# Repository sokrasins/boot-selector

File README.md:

# Boot Selector
 
 Choose your booting OS, now with more RP2040!

 Inspired by

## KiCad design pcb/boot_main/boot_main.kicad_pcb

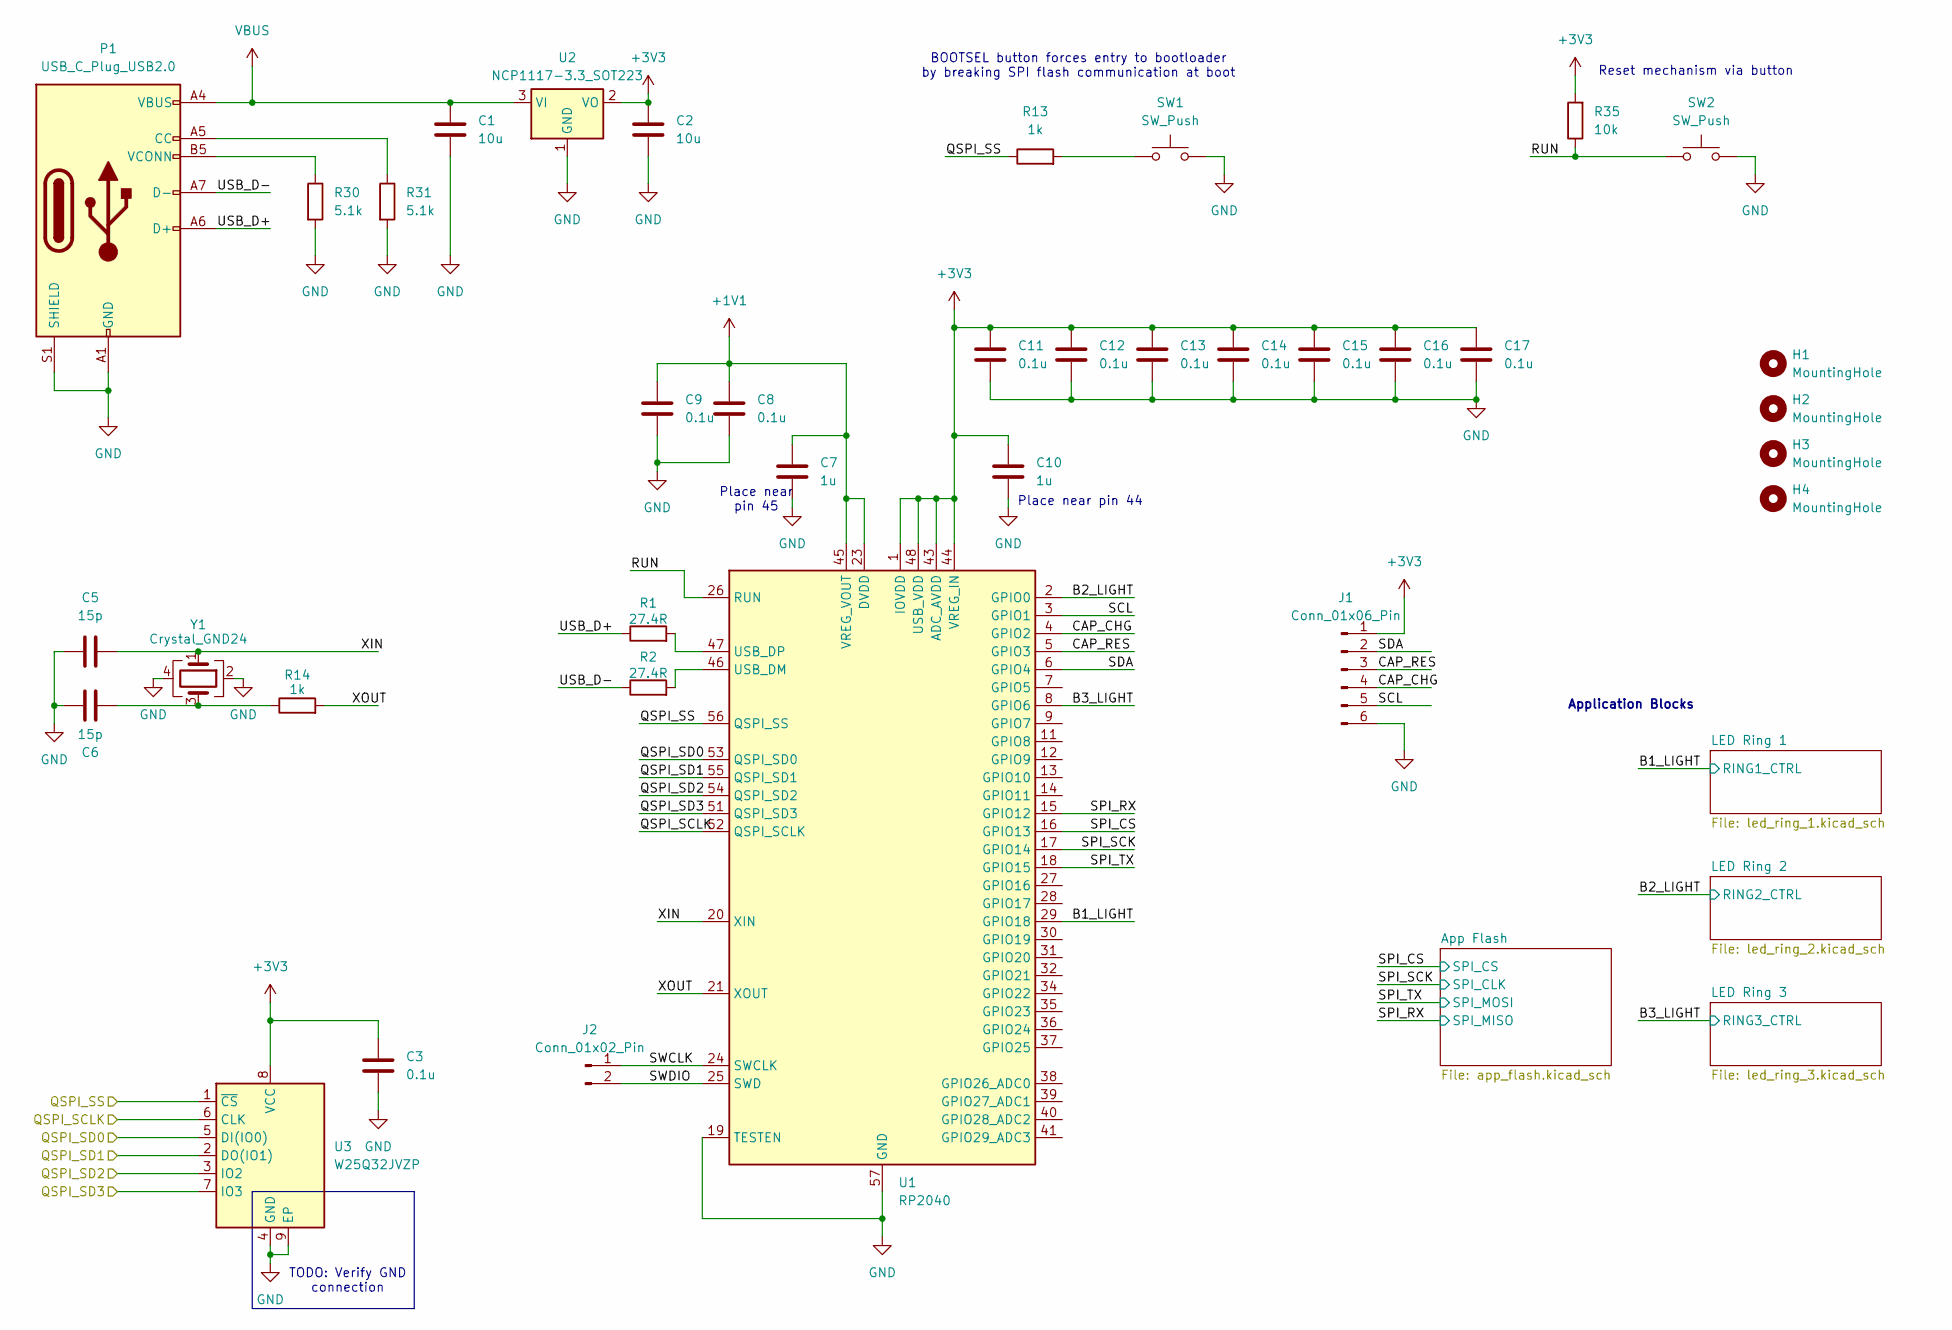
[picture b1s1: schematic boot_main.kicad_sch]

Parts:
C1, C2: 10u; C_0603_1608Metric
C3: 0.1u; C_0603_1608Metric
C5, C6: 15p; C_0402_1005Metric
C7, C10: 1u; C_0402_1005Metric
C8, C9, C11, C12, C13, C14, C15, C16, C17: 0.1u; C_0402_1005Metric
H1, H2, H3, H4: MountingHole; MountingHole_3.2mm_M3
J1: Conn_01x06_Pin; Hirose_FH12-6S-0.5SH_1x06-1MP_P0.50mm_Horizontal
J2: Conn_01x02_Pin; PinHeader_1x02_P2.54mm_Vertical
P1: USB_C_Plug_USB2.0; USB_C_Receptacle_GCT_USB4115-03-C
R1, R2: 27.4R; R_0402_1005Metric
R13: 1k; R_0603_1608Metric
R14: 1k; R_0402_1005Metric
R30, R31: 5.1k; R_0402_1005Metric
R35: 10k; R_0603_1608Metric
SW1, SW2: SW_Push; SW_Push_1P1T_NO_6x6mm_H9.5mm
U1: RP2040; QFN-56-1EP_7x7mm_P0.4mm_EP3.2x3.2mm
U2: NCP1117-3.3_SOT223; SOT-223-3_TabPin2
U3: W25Q32JVZP; WSON-8-1EP_6x5mm_P1.27mm_EP3.4x4.3mm
Y1: Crystal_GND24; Crystal_SMD_3225-4Pin_3.2x2.5mm

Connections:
+1V1: C7.1, C8.1, C9.1, U1.23 (DVDD), U1.45 (VREG_VOUT), U1.50 (DVDD)
+3V3: C2.1, C3.1, C10.1, C11.1, C12.1, C13.1, C14.1, C15.1, C16.1, C17.1, J1.1, R35.2, U1.1 (IOVDD), U1.10 (IOVDD), U1.22 (IOVDD), U1.33 (IOVDD), U1.42 (IOVDD), U1.43 (ADC_AVDD), U1.44 (VREG_IN), U1.48 (USB_VDD), U1.49 (IOVDD), U2.2 (VO), U3.8 (VCC); also elsewhere on the board
/B1_LIGHT: U1.29 (GPIO18); also elsewhere on the board
/B2_LIGHT: U1.2 (GPIO0); also elsewhere on the board
/B3_LIGHT: U1.8 (GPIO6); also elsewhere on the board
/CAP_CHG: J1.4, U1.4 (GPIO2)
/CAP_RES: J1.3, U1.5 (GPIO3)
/QSPI_SCLK: U1.52 (QSPI_SCLK), U3.6 (CLK)
/QSPI_SD0: U1.53 (QSPI_SD0), U3.5 (DI(IO0))
/QSPI_SD1: U1.55 (QSPI_SD1), U3.2 (DO(IO1))
/QSPI_SD2: U1.54 (QSPI_SD2), U3.3 (IO2)
/QSPI_SD3: U1.51 (QSPI_SD3), U3.7 (IO3)
/QSPI_SS: R13.1, U1.56 (QSPI_SS), U3.1 (~CS)
/RUN: R35.1, SW2.1, U1.26 (RUN)
/SCL: J1.5, U1.3 (GPIO1)
/SDA: J1.2, U1.6 (GPIO4)
/SPI_CS: U1.16 (GPIO13); also elsewhere on the board
/SPI_RX: U1.15 (GPIO12); also elsewhere on the board
/SPI_SCK: U1.17 (GPIO14); also elsewhere on the board
/SPI_TX: U1.18 (GPIO15); also elsewhere on the board
/SWCLK: J2.1, U1.24 (SWCLK)
/SWDIO: J2.2, U1.25 (SWD)
/USB_D+: P1.A6 (D+), R1.1
/USB_D-: P1.A7 (D-), R2.1
/XIN: C5.2, U1.20 (XIN), Y1.1
/XOUT: R14.2, U1.21 (XOUT)
GND: C1.2, C2.2, C3.2, C5.1, C6.1, C7.2, C8.2, C9.2, C10.2, C11.2, C12.2, C13.2, C14.2, C15.2, C16.2, C17.2, J1.6, P1.A1 (GND), P1.A12 (GND), P1.B1 (GND), P1.B12 (GND), P1.S1 (SHIELD), R30.2, R31.2, SW1.2, SW2.2, U1.19 (TESTEN), U1.57 (GND), U2.1 (GND), U3.4 (GND), U3.9 (EP), Y1.2, Y1.4; also elsewhere on the board
unnamed: C6.2, R14.1, Y1.3
unnamed: P1.A5 (CC), R31.1
unnamed: P1.B5 (VCONN), R30.1
unnamed: R13.2, SW1.1
unnamed: R2.2, U1.46 (USB_DM)
unnamed: R1.2, U1.47 (USB_DP)

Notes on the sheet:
BOOTSEL button forces entry to bootloader by breaking SPI flash communication at boot
TODO: Verify GND connection
Place near pin 44
Place near pin 45
Reset mechanism via button
Application Blocks

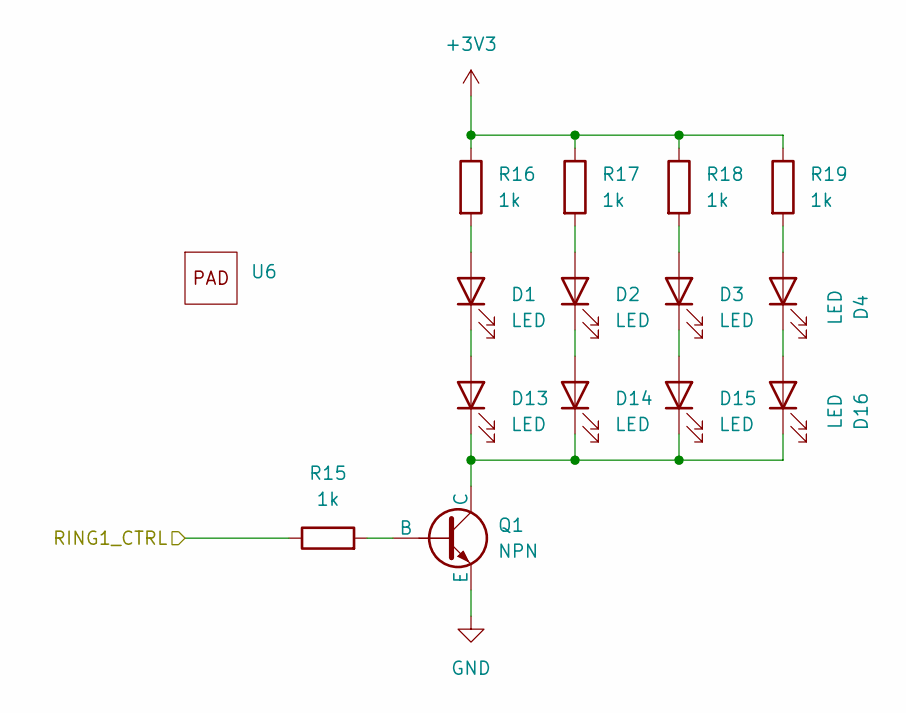
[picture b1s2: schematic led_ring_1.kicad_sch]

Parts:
D1, D2, D3, D4, D13, D14, D15, D16: LED; LED_1206_3216Metric
Q1: NPN; SOT-323_SC-70
R15, R16, R17, R18, R19: 1k; R_0603_1608Metric
U6: square_20x20mm_guide

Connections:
/B1_LIGHT: R15.1; also elsewhere on the board
GND: Q1.3 (E); also elsewhere on the board
unnamed: D1.2 (A), R16.2
unnamed: D1.1 (K), D13.2 (A)
unnamed: D2.2 (A), R17.2
unnamed: D3.2 (A), R18.2
unnamed: D4.2 (A), R19.2
unnamed: D13.1 (K), D14.1 (K), D15.1 (K), D16.1 (K), Q1.1 (C)
unnamed: D2.1 (K), D14.2 (A)
unnamed: D3.1 (K), D15.2 (A)
unnamed: D4.1 (K), D16.2 (A)
unnamed: Q1.2 (B), R15.2

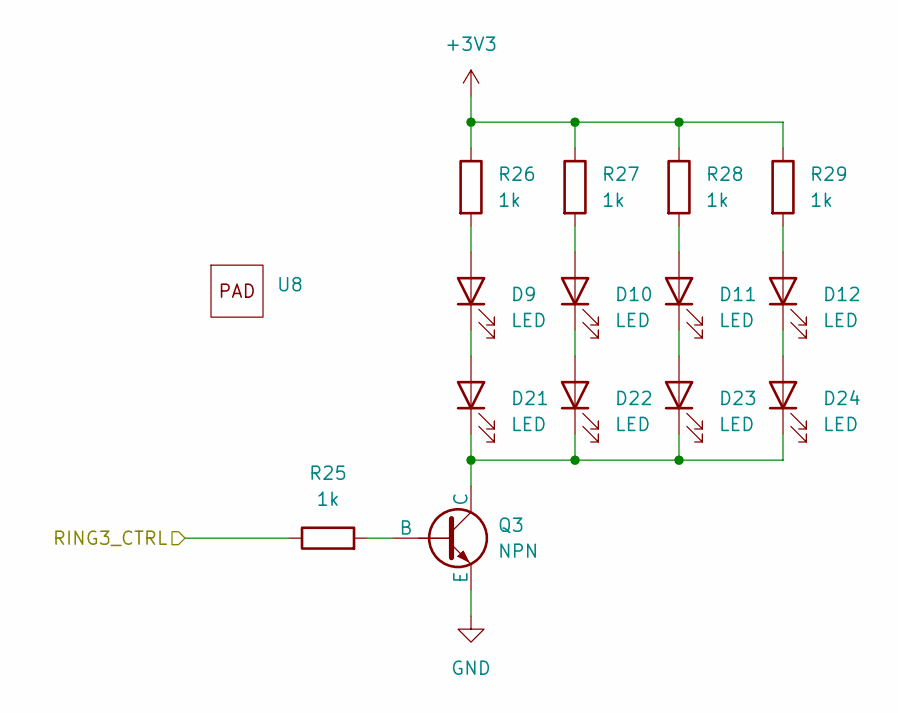
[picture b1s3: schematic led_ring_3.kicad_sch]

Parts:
D9, D10, D11, D12, D21, D22, D23, D24: LED; LED_1206_3216Metric
Q3: NPN; SOT-323_SC-70
R25, R26, R27, R28, R29: 1k; R_0603_1608Metric
U8: square_20x20mm_guide

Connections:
/B3_LIGHT: R25.1; also elsewhere on the board
GND: Q3.3 (E); also elsewhere on the board
unnamed: D9.2 (A), R26.2
unnamed: D10.2 (A), R27.2
unnamed: D10.1 (K), D22.2 (A)
unnamed: D11.2 (A), R28.2
unnamed: D11.1 (K), D23.2 (A)
unnamed: D12.2 (A), R29.2
unnamed: D12.1 (K), D24.2 (A)
unnamed: D9.1 (K), D21.2 (A)
unnamed: D21.1 (K), D22.1 (K), D23.1 (K), D24.1 (K), Q3.1 (C)
unnamed: Q3.2 (B), R25.2

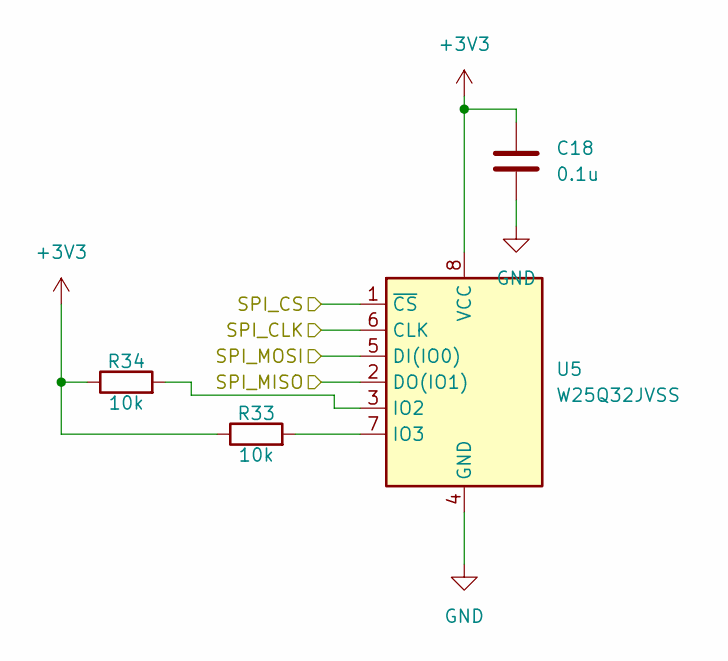
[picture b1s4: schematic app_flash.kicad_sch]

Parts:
C18: 0.1u; C_0603_1608Metric
R33, R34: 10k; R_0603_1608Metric
U5: W25Q32JVSS; SOIC-8_5.23x5.23mm_P1.27mm

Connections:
+3V3: C18.1, R33.1, R34.1, U5.8 (VCC); also elsewhere on the board
/SPI_CS: U5.1 (~CS); also elsewhere on the board
/SPI_RX: U5.2 (DO(IO1)); also elsewhere on the board
/SPI_SCK: U5.6 (CLK); also elsewhere on the board
/SPI_TX: U5.5 (DI(IO0)); also elsewhere on the board
GND: C18.2, U5.4 (GND); also elsewhere on the board
unnamed: R34.2, U5.3 (IO2)
unnamed: R33.2, U5.7 (IO3)

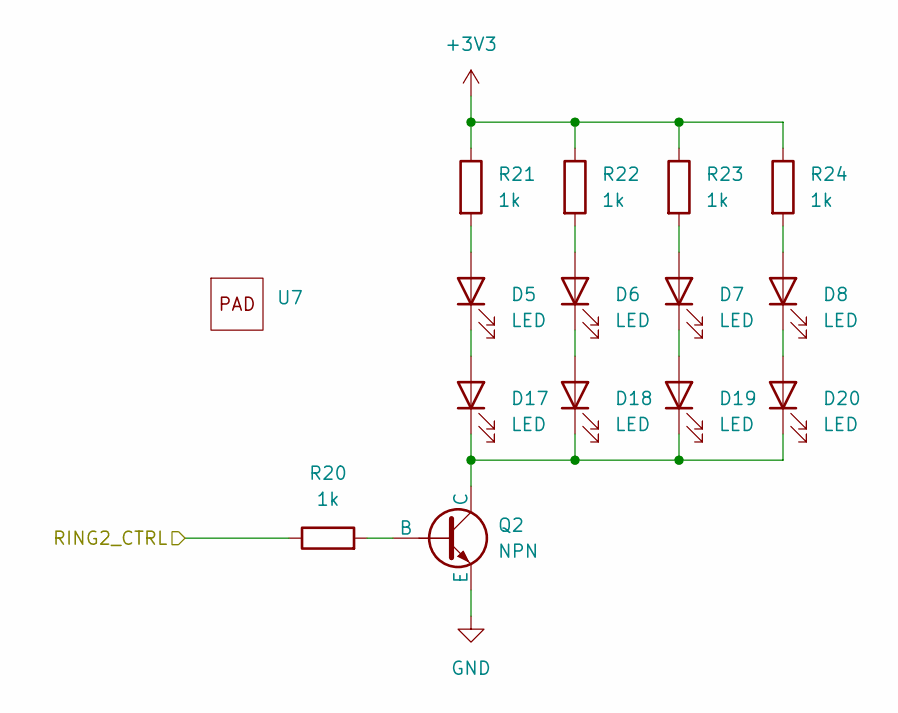
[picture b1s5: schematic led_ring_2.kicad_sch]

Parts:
D5, D6, D7, D8, D17, D18, D19, D20: LED; LED_1206_3216Metric
Q2: NPN; SOT-323_SC-70
R20, R21, R22, R23, R24: 1k; R_0603_1608Metric
U7: square_20x20mm_guide

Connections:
/B2_LIGHT: R20.1; also elsewhere on the board
GND: Q2.3 (E); also elsewhere on the board
unnamed: D5.2 (A), R21.2
unnamed: D6.2 (A), R22.2
unnamed: D7.2 (A), R23.2
unnamed: D8.2 (A), R24.2
unnamed: D5.1 (K), D17.2 (A)
unnamed: D17.1 (K), D18.1 (K), D19.1 (K), D20.1 (K), Q2.1 (C)
unnamed: D6.1 (K), D18.2 (A)
unnamed: D7.1 (K), D19.2 (A)
unnamed: D8.1 (K), D20.2 (A)
unnamed: Q2.2 (B), R20.2

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
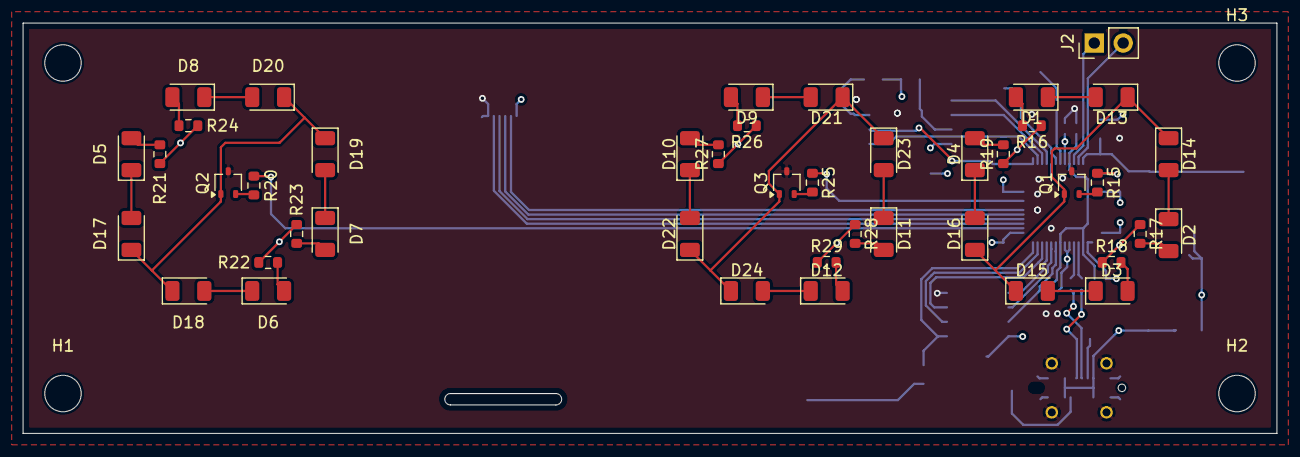
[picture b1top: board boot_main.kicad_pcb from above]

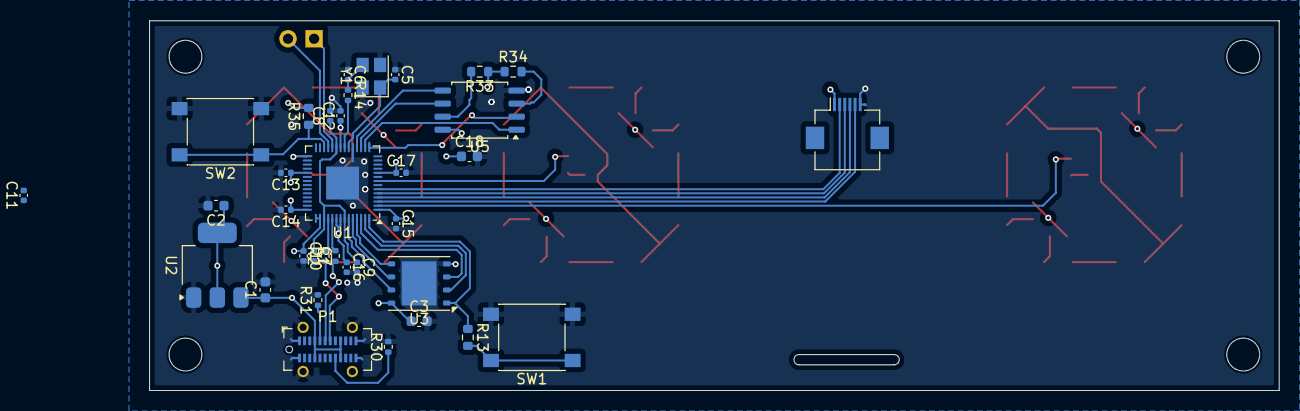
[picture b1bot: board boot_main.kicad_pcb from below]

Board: 4 copper layers, 110.0 x 36.0 mm, 85 parts (35 on the bottom side), 66 nets.

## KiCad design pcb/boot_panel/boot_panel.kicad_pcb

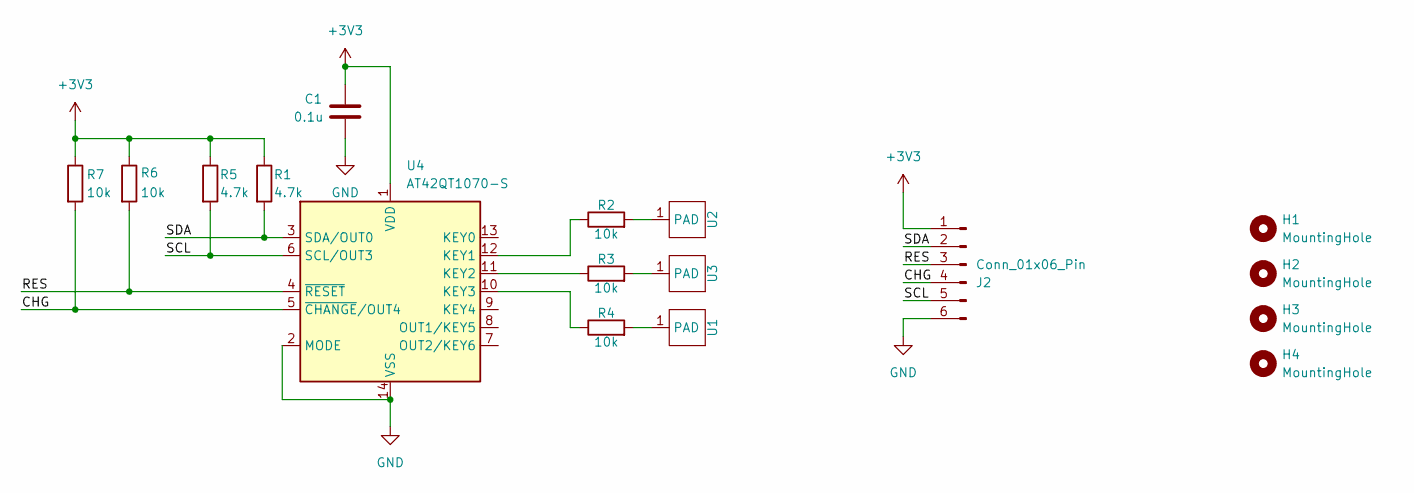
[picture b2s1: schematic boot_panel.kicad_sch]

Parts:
C1: 0.1u; C_0603_1608Metric_Pad1.08x0.95mm_HandSolder
H1, H2, H3, H4: MountingHole; MountingHole_3.2mm_M3
J2: Conn_01x06_Pin; Hirose_FH12-6S-0.5SH_1x06-1MP_P0.50mm_Horizontal
R1, R5: 4.7k; R_0603_1608Metric_Pad0.98x0.95mm_HandSolder
R2, R3, R4, R6, R7: 10k; R_0603_1608Metric_Pad0.98x0.95mm_HandSolder
U1, U2, U3: square_20x20mm
U4: AT42QT1070-S; SOIC-14_3.9x8.7mm_P1.27mm

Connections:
+3V3: C1.1, J2.1, R1.1, R5.1, R6.1, R7.1, U4.1 (VDD)
/CHG: J2.4, R7.2, U4.5 (~CHANGE/OUT4)
/RES: J2.3, R6.2, U4.4 (~RESET)
/SCL: J2.5, R5.2, U4.6 (SCL/OUT3)
/SDA: J2.2, R1.2, U4.3 (SDA/OUT0)
GND: C1.2, J2.6, U4.2 (MODE), U4.14 (VSS)
unnamed: R4.2, U1.1 (PAD)
unnamed: R2.2, U2.1 (PAD)
unnamed: R3.2, U3.1 (PAD)
unnamed: R2.1, U4.12 (KEY1)
unnamed: R3.1, U4.11 (KEY2)
unnamed: R4.1, U4.10 (KEY3)

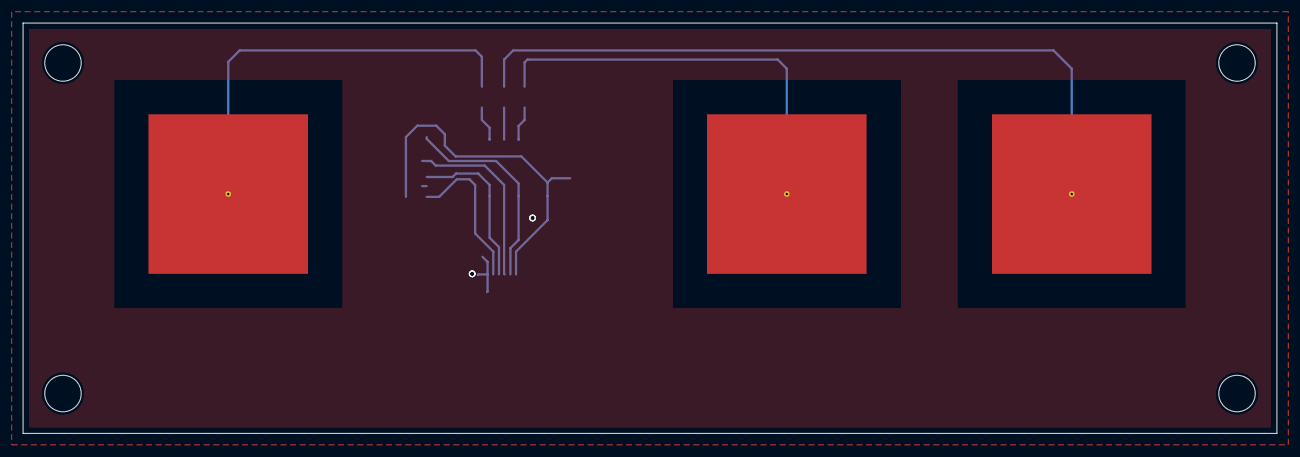
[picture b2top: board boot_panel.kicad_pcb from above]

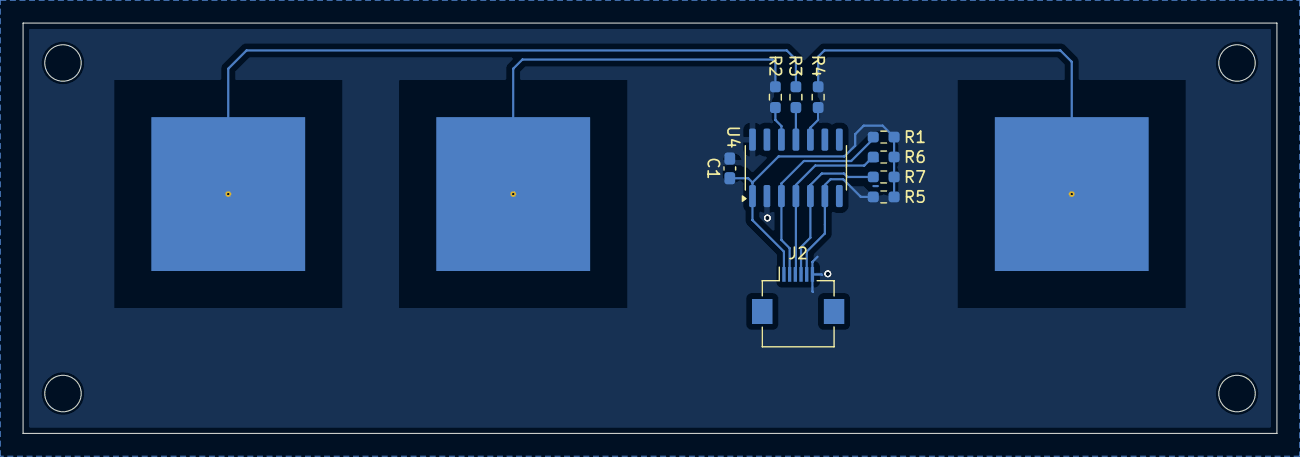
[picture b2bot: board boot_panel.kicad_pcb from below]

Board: 2 copper layers, 110.0 x 36.0 mm, 17 parts (10 on the bottom side), 12 nets.

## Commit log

2024-07-30 reorg, added maindboard sch
2024-07-30 update submodules
2024-07-30 readd submodule
2024-08-01 More schematic
2024-08-02 More sch, added datasheets
2024-08-02 Add cap sense driver
2024-08-03 Assign footprints
2024-08-03 push parts around
2024-08-03 Some initial layout
2024-08-03 Added front panel board
2024-08-04 move panel connector to fpc
2024-08-05 MOre layout
2024-08-06 move cap sense ic to front panel
2024-08-16 Reorg, start building out cap sense thing
2024-08-17 Tweak i2c settings
2024-08-17 Change voltage rail on LEDs
2024-08-22 Basic communication with the cap sensor
2024-08-22 Added key class
2024-08-22 Toggle switch function working
2024-08-22 Flash storage doesn't work, but bouncing USB connection does
2024-08-23 Reorg and refactor
